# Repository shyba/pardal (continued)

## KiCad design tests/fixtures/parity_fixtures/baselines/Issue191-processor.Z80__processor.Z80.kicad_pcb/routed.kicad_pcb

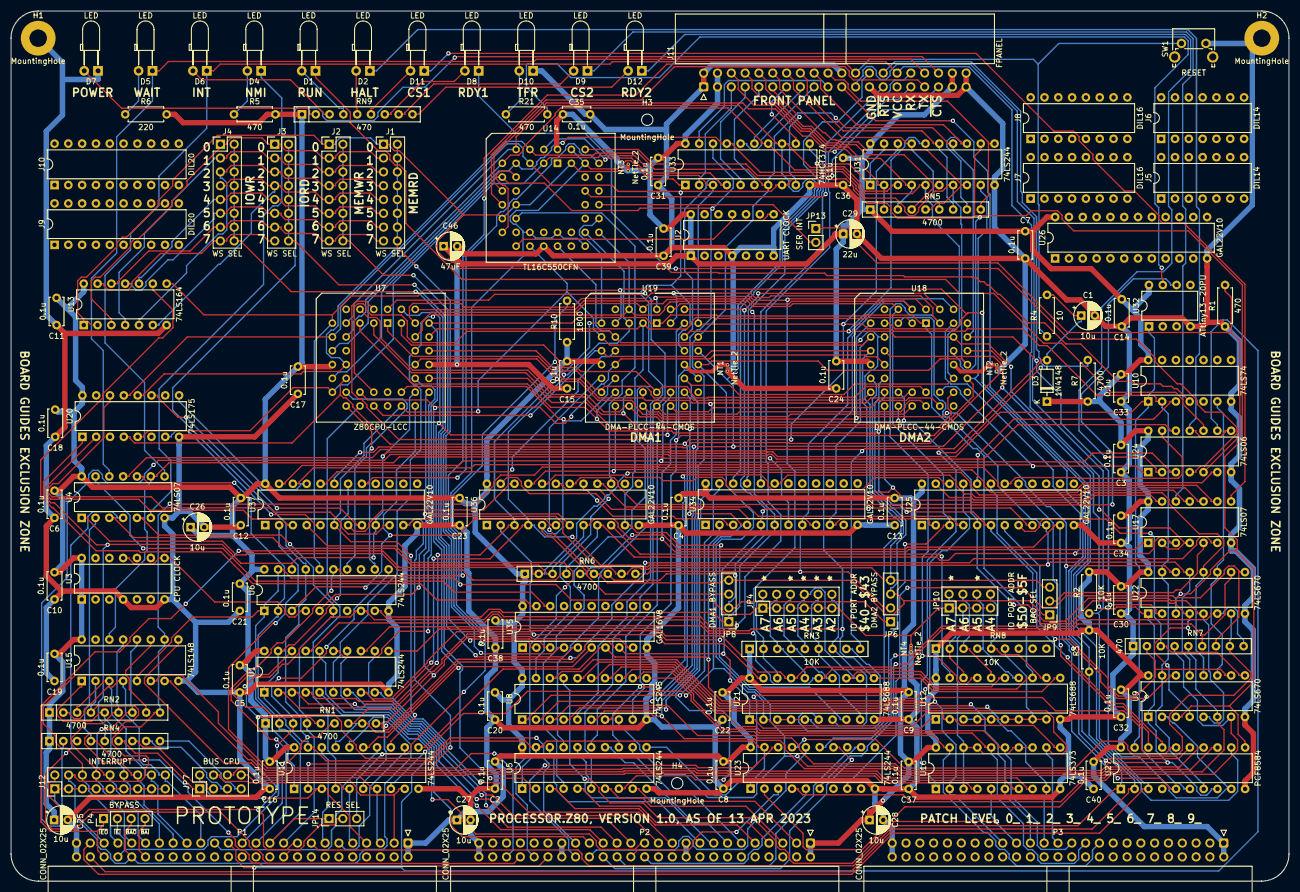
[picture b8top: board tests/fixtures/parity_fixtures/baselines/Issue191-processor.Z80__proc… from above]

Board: 2 copper layers, 235.0 x 160.0 mm, 138 parts (0 on the bottom side), 244 nets.

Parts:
C1, C25, C26, C27, C28: 10u; CP_Radial_D5.0mm_P2.50mm
C2, C3, C4, C5, C6, C7, C8, C9, C10, C11, C12, C13, C14, C15, C16, C17, C18, C19, C20, C21, C22, C23, C24, C30, C31, C32, C33, C34, C35, C36, C37, C38, C39, C40: 0.1u; C_Disc_D5.0mm_W2.5mm_P5.00mm
C29: 22u; CP_Radial_D5.0mm_P2.50mm
C46: 47uF; CP_Radial_D5.0mm_P2.50mm
D1, D2, D4, D5, D6, D7, D8, D9, D10, D11, D12: LED; LED_D3.0mm_Horizontal_O3.81mm_Z2.0mm
D3: 1N4148; D_DO-35_SOD27_P7.62mm_Horizontal
H1, H2: MountingHole; MountingHole_3.2mm_M3_Pad
H3, H4: MountingHole; MountingHole_2.1mm
J1, J2, J3, J4: WS SEL; PinHeader_2x08_P2.54mm_Vertical
J5, J6: DIL14; DIP-14_W7.62mm
J7, J8: DIL16; DIP-16_W7.62mm
J9, J10: DIL20; DIP-20_W7.62mm
J11: FPANEL; IDC-Header_2x20_P2.54mm_Horizontal
J12: INTERRUPT; PinHeader_2x09_P2.54mm_Vertical
JP4: IO PORT ADDR; PinHeader_2x06_P2.54mm_Vertical
JP6: DMA2 BYPASS; PinHeader_1x04_P2.54mm_Vertical
JP7: BUS CPU; PinHeader_2x04_P2.54mm_Vertical
JP8: DMA1 BYPASS; PinHeader_1x04_P2.54mm_Vertical
JP9: BAO SEL; PinHeader_1x03_P2.54mm_Vertical
JP10: IO PORT ADDR; PinHeader_2x04_P2.54mm_Vertical
JP13: SER INT; PinHeader_1x02_P2.54mm_Vertical
JP14: RES SEL; PinHeader_1x03_P2.54mm_Vertical
NT1, NT2, NT3, NT4: NetTie_2; NetTie-2_THT_Pad0.3mm
P1, P2, P3: CONN_02X25; IDC-Header_2x25_P2.54mm_Horizontal
P4: BYPASS; PinHeader_1x04_P2.54mm_Vertical
R1, R5, R21: 470; R_Axial_DIN0207_L6.3mm_D2.5mm_P7.62mm_Horizontal
R2, R3: 10K; R_Axial_DIN0207_L6.3mm_D2.5mm_P7.62mm_Horizontal
R4: 10; R_Axial_DIN0207_L6.3mm_D2.5mm_P7.62mm_Horizontal
R6: 220; R_Axial_DIN0207_L6.3mm_D2.5mm_P7.62mm_Horizontal
R7: 4700; R_Axial_DIN0207_L6.3mm_D2.5mm_P7.62mm_Horizontal
R10: 1800; R_Axial_DIN0207_L6.3mm_D2.5mm_P7.62mm_Horizontal
RN1, RN2, RN4, RN5, RN6: 4700; R_Array_SIP9
RN3, RN8: 10K; R_Array_SIP9
RN7, RN9: 470; R_Array_SIP9
SW1: RESET; SW_Tactile_SPST_Angled_PTS645Vx58-2LFS
U1, U5, U6, U11, U23, U31: 74LS244; DIP-20_W7.62mm
U2: UART CLOCK; DIP-14_W7.62mm
U3: CPU CLOCK; DIP-14_W7.62mm
U4, U17: 74LS07; DIP-14_W7.62mm
U7: Z80CPU-LCC; PLCC-44_THT-Socket
U8: 74LS245; DIP-20_W7.62mm
U9, U22: 74LS670; DIP-16_W7.62mm
U10: 74LS74; DIP-14_W7.62mm
U12, U21: 74LS688; DIP-20_W7.62mm
U13: 74LS164; DIP-14_W7.62mm
U14: TL16C550CFN; PLCC-44_THT-Socket
U15: 74LS148; DIP-16_W7.62mm
U16: 74LS373; DIP-20_W7.62mm
U18, U19: DMA-PLCC-44-CMOS; PLCC-44_THT-Socket
U20: 74LS175; DIP-16_W7.62mm
U24: 74LS06; DIP-14_W7.62mm
U25, U26, U34, U36, U37: GAL22V10; DIP-24_W7.62mm
U27: PCF8584; DIP-20_W7.62mm
U32: ATtiny13-20PU; DIP-8_W7.62mm
U33: 74HCT374; DIP-20_W7.62mm
U35: GAL16V8; DIP-20_W7.62mm

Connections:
10KA: C1.1, D3.2 (A), R4.2, RN3.9 (R8), U4.11
470A: D7.2 (A), RN9.2 (R1)
470B: D6.2 (A), RN9.3 (R2)
470C: D1.2 (A), RN9.4 (R3)
470D: D2.2 (A), RN9.5 (R4)
470E: D11.2 (A), RN9.6 (R5)
470F: D8.2 (A), RN9.7 (R6)
470G: D9.2 (A), RN9.8 (R7)
470H: D12.2 (A), RN9.9 (R8)
+12V: P2.19, P2.20
-12V: P2.37, P2.38
/DMA/GND-DMA1: NT1.2, U19.34 (GND)
/DMA/GND-DMA2: NT2.2, U18.34 (GND)
/fpanel/FP-D0: J11.6, RN5.2 (R1), U31.2 (1A0)
/fpanel/FP-D1: J11.8, RN5.3 (R2), U31.4 (1A1)
/fpanel/FP-D2: J11.10, RN5.4 (R3), U31.6 (1A2)
/fpanel/FP-D3: J11.12, RN5.5 (R4), U31.8 (1A3)
/fpanel/FP-D4: J11.14, RN5.6 (R5), U31.17 (2A0)
/fpanel/FP-D5: J11.16, RN5.7 (R6), U31.15 (2A1)
/fpanel/FP-D6: J11.18, RN5.8 (R7), U31.13 (2A2)
/fpanel/FP-D7: J11.20, RN5.9 (R8), U31.11 (2A3)
/waitstate/1WS: J1.3, J2.3, J3.1, J4.1, U13.3 (Q0)
/waitstate/2WS: J1.5, J2.5, J3.3, J4.3, U13.4 (Q1)
/waitstate/3WS: J1.7, J2.7, J3.5, J4.5, U13.5 (Q2)
/waitstate/4WS: J1.9, J2.9, J3.7, J4.7, U13.6 (Q3)
/waitstate/5WS: J1.11, J2.11, J3.9, J4.9, U13.10 (Q4)
/waitstate/6WS: J1.13, J2.13, J3.11, J4.11, U13.11 (Q5)
/waitstate/7WS: J1.15, J2.15, J3.13, J4.13, U13.12 (Q6)
/waitstate/8WS: J3.15, J4.15, U13.13 (Q7)
A0: P2.35, U1.18 (1Y0)
A1: P2.33, U1.16 (1Y1)
A2: P2.31, U1.14 (1Y2)
A3: P2.29, U1.12 (1Y3)
A4: P2.27, U1.3 (2Y0)
A5: P2.25, U1.5 (2Y1)
A6: P2.23, U1.7 (2Y2)
A7: P2.21, U1.9 (2Y3)
A8: P2.17, U5.18 (1Y0)
A9: P2.15, U5.16 (1Y1)
A10: P2.13, U5.14 (1Y2)
A11: P2.11, U5.12 (1Y3)
A12: P2.9, U5.3 (2Y0)
A13: P2.7, U5.5 (2Y1)
A14: P2.5, U5.7 (2Y2)
A15: P2.3, U5.9 (2Y3)
A16: P2.36, U23.18 (1Y0)
A17: P2.34, U23.16 (1Y1)
A18: P2.32, U23.14 (1Y2)
A19: P2.30, U23.12 (1Y3)
A20: P2.28, U23.3 (2Y0)
A21: P2.26, U23.5 (2Y1)
BUSACK: U1.1 (1OE), U1.19 (2OE), U5.1 (1OE), U5.19 (2OE), U11.19 (2OE), U23.1 (1OE), U23.19 (2OE), U37.18 (O5)
CLK: P1.15, U6.16 (1Y1), U7.7 (CLK), U13.8 (CP), U18.8 (CLK), U19.8 (CLK), U27.1 (CLK)
CPU-A0: U1.2 (1A0), U7.34 (A0), U9.14 (Wa), U14.31 (A0), U18.7 (A0), U19.7 (A0), U22.14 (Wa), U27.6 (A0), U36.3 (I2)
CPU-A1: U1.4 (1A1), U7.35 (A1), U9.13 (Wb), U14.30 (A1), U18.5 (A1), U19.5 (A1), U22.13 (Wb), U25.10 (I9), U36.4 (I3)
CPU-A2: U1.6 (1A2), U7.36 (A2), U14.29 (A2), U18.4 (A2), U19.4 (A2), U21.6 (P2), U25.3 (I2)
CPU-A3: U1.8 (1A3), U7.37 (A3), U18.3 (A3), U19.3 (A3), U21.8 (P3), U36.11 (I10)
CPU-A4: U1.17 (2A0), U7.38 (A4), U12.11 (P4), U18.2 (A4), U19.2 (A4), U21.11 (P4)
CPU-A5: U1.15 (2A1), U7.39 (A5), U12.13 (P5), U18.1 (A5), U19.1 (A5), U21.13 (P5)
CPU-A6: U1.13 (2A2), U7.40 (A6), U12.15 (P6), U18.44 (A6), U19.44 (A6), U21.15 (P6)
CPU-A7: U1.11 (2A3), U7.41 (A7), U12.17 (P7), U18.43 (A7), U19.43 (A7), U21.17 (P7)
CPU-A8: U5.2 (1A0), U7.42 (A8), U18.26 (A8), U19.26 (A8)
CPU-A9: U5.4 (1A1), U7.43 (A9), U18.25 (A9), U19.25 (A9)
CPU-A10: U5.6 (1A2), U7.44 (A10), U18.24 (A10), U19.24 (A10)
CPU-A11: U5.8 (1A3), U7.1 (A11), U18.23 (A11), U19.23 (A11)
CPU-A12: U5.17 (2A0), U7.2 (A12), U18.22 (A12), U19.22 (A12)
CPU-A13: U5.15 (2A1), U7.3 (A13), U18.21 (A13), U19.21 (A13)
CPU-A14: U7.4 (A14), U9.5 (Ra), U18.20 (A14), U19.20 (A14), U22.5 (Ra), U25.5 (I4)
CPU-A15: U7.5 (A15), U9.4 (Rb), U18.19 (A15), U19.19 (A15), U22.4 (Rb), U25.6 (I5)
CPU-D0: U7.16 (D0), U8.2 (A0), U9.15 (D1), U10.2 (D), U14.2 (D0), U18.39 (D0), U19.39 (D0), U20.4 (D0), U22.15 (D1), U27.7 (D0), U31.18 (1Y0), U33.3 (D0)
CPU-D1: U7.17 (D1), U8.3 (A1), U9.1 (D2), U14.3 (D1), U18.38 (D1), U19.38 (D1), U20.5 (D1), U22.1 (D2), U27.8 (D1), U31.16 (1Y1), U33.4 (D1)
CPU-D2: U7.14 (D2), U8.4 (A2), U9.2 (D3), U14.4 (D2), U18.37 (D2), U19.37 (D2), U20.12 (D2), U22.2 (D3), U27.9 (D2), U31.14 (1Y2), U33.7 (D2)
CPU-D3: U7.9 (D3), U8.5 (A3), U9.3 (D4), U14.5 (D3), U18.36 (D3), U19.36 (D3), U20.13 (D3), U22.3 (D4), U27.11 (D3), U31.12 (1Y3), U33.8 (D3)
CPU-D4: U7.8 (D4), U8.6 (A4), U14.6 (D4), U18.35 (D4), U19.35 (D4), U27.12 (D4), U31.3 (2Y0), U33.13 (D4)
CPU-D5: U7.10 (D5), U8.7 (A5), U14.7 (D5), U18.32 (D5), U19.32 (D5), U27.13 (D5), U31.5 (2Y1), U33.14 (D5)
CPU-D6: U7.11 (D6), U8.8 (A6), U14.8 (D6), U18.33 (D6), U19.33 (D6), U27.14 (D6), U31.7 (2Y2), U33.17 (D6)
CPU-D7: U7.15 (D7), U8.9 (A7), U14.9 (D7), U18.31 (D7), U19.31 (D7), U27.15 (D7), U31.9 (2Y3), U33.18 (D7)
D0: P3.33, U8.18 (B0), U16.2 (O0)
D1: P3.31, U8.17 (B1), U16.5 (O1)
D2: P3.29, U8.16 (B2), U16.6 (O2)
D3: P3.27, U8.15 (B3), U16.9 (O3)
D4: P3.25, U8.14 (B4), U16.12 (O4)
D5: P3.23, U8.13 (B5), U16.15 (O5)
D6: P3.21, U8.12 (B6), U16.16 (O6)
D7: P3.19, U8.11 (B7), U16.19 (O7)
DATA-DIR: U8.1 (A->B), U34.23 (O0)
DATA_XFER: U32.6 (PB1), U36.18 (O5)
DMA-RDY1: U19.27 (RDY), U24.3, U37.23 (O0)
DMA-RDY2: U18.27 (RDY), U24.1, U37.22 (O1)
FP-LATCH-WR: U33.11 (Cp), U34.20 (O3)
GND: C1.2, C2.2, C3.2, C4.2, C5.2, C6.2, C7.2, C8.2, C9.2, C10.2, C11.2, C12.2, C13.2, C14.2, C15.2, C16.2, C17.2, C18.2, C19.2, C20.2, C21.2, C22.2, C23.2, C24.2, C25.2, C26.2, C27.2, C28.2, C29.2, C30.2, C31.2, C32.2, C33.2, C34.2, C35.2, C36.2, C37.2, C38.2, C39.2, C40.2, C46.2, D7.1 (K), D10.1 (K), H1.1, H2.1, J11.1, J11.2, J11.22, J11.25, J11.39, J11.40, NT1.1, NT2.1, NT4.1, P1.49, P1.50, P2.49, P2.50, P3.49, P3.50, R1.1, RN7.1 (common), SW1.2, U1.10 (GND), U2.4, U2.7, U3.4, U3.7, U4.7 (GND), U5.10 (GND), U6.10 (GND), U7.33 (GND), U8.10 (GND), U9.8 (GND), U10.7 (GND), U11.10 (GND), U12.10 (GND), U13.7 (GND), U14.22 (GND), U15.8 (GND), U16.10 (GND), U17.7 (GND), U20.8 (GND), U21.10 (GND), U22.8 (GND), U23.10 (GND), U24.7 (GND), U25.12 (GND), U26.12 (GND), U27.10 (VSS), U31.10 (GND), U32.4 (GND), U33.10 (GND), U34.12 (GND), U35.10 (GND), U36.12 (GND), U37.12 (GND)
I2C_SCL: J11.23, P1.47, R2.1, U27.3 (SCL)
I2C_SDA: J11.21, P1.48, R3.1, U27.2 (SDA)
INT: JP13.1 (A), R1.2, U24.5
INT-I2C: U24.13, U25.18 (O5)
IO-SEL: U34.3 (I2), U36.17 (O6)
unnamed: D1.1 (K), U24.10
unnamed: D2.1 (K), U24.8, U24.11
unnamed: D4.1 (K), U4.6
unnamed: D4.2 (A), R5.1
unnamed: D5.2 (A), R6.1
unnamed: D8.1 (K), U24.4
unnamed: D9.1 (K), U17.12
unnamed: D10.2 (A), R21.1
unnamed: D11.1 (K), U17.8
unnamed: D12.1 (K), U24.2
unnamed: J11.5, U33.2 (O0)
unnamed: J11.7, U33.5 (O1)
unnamed: J11.9, U33.6 (O2)
unnamed: J11.11, U33.9 (O3)
unnamed: J11.13, U33.12 (O4)
unnamed: J11.15, U33.15 (O5)
unnamed: J11.17, U33.16 (O6)
unnamed: J11.19, U33.19 (O7)
unnamed: J12.1, J12.3, J12.5, J12.7, J12.9, J12.11, J12.13, J12.15, J12.17, U24.12
unnamed: JP4.2, RN3.2 (R1), U21.18 (R7)
unnamed: JP4.4, RN3.3 (R2), U21.16 (R6)
unnamed: JP4.6, RN3.4 (R3), U21.14 (R5)
unnamed: JP4.8, RN3.5 (R4), U21.12 (R4)
unnamed: JP4.10, RN3.6 (R5), U21.9 (R3)
unnamed: JP4.12, RN3.7 (R6), U21.7 (R2)
unnamed: JP7.1, RN4.6 (R5)
unnamed: JP7.3, RN4.7 (R6)
unnamed: JP7.5, RN4.8 (R7)
unnamed: JP7.7, RN4.9 (R8)
unnamed: JP9.2, U17.5
unnamed: JP10.2, RN8.2 (R1), U12.18 (R7)
unnamed: JP10.4, RN8.3 (R2), U12.16 (R6)
unnamed: JP10.6, RN8.4 (R3), U12.14 (R5)
unnamed: JP10.8, RN8.5 (R4), U12.12 (R4)
unnamed: JP13.2 (B), U14.33 (INTR)
unnamed: R21.2, U32.7 (PB2)
unnamed: RN3.8 (R7), U21.3 (R0), U21.4 (P1), U21.5 (R1)
unnamed: RN8.6 (R5), U12.3 (R0), U12.4 (P1), U12.5 (R1), U12.6 (P2), U12.7 (R2), U12.8 (P3), U12.9 (R3)
unnamed: U14.10 (RCLK), U14.17 (~BAUDOUT)
unnamed: U15.6 (S2), U16.8 (D3)
unnamed: U15.7 (S1), U16.7 (D2)
unnamed: U15.9 (S0), U16.4 (D1)
ONE: J1.1, J2.1, NT3.2, U10.4 (~S), U13.1 (DSA), U13.2 (DSB), U14.14 (CS0), U14.15 (CS1), U14.43 (~RI)
RAW-CLK: U3.8, U3.11, U6.4 (1A1)
RDY_Q0: U20.2 (Q0), U37.3 (I2)
RDY_Q1: U20.7 (Q1), U37.5 (I4)
READY: U4.13, U35.18 (IO2)
RESET: U14.39 (MR), U37.17 (O6)
RX: J11.31, U14.11 (SIN)
SEL-A14: U5.13 (2A2), U25.22 (O1)
SEL-A15: U5.11 (2A3), U25.21 (O2)
TX: J11.33, U14.13 (SOUT)
UART-CLK: U2.8, U2.11, U14.18 (XIN)
VCC: C2.1, C3.1, C4.1, C5.1, C6.1, C7.1, C8.1, C9.1, C10.1, C11.1, C12.1, C13.1, C14.1, C15.1, C16.1, C17.1, C18.1, C19.1, C20.1, C21.1, C22.1, C23.1, C24.1, C25.1, C26.1, C27.1, C28.1, C29.1, C30.1, C31.1, C32.1, C33.1, C34.1, C35.1, C36.1, C37.1, C38.1, C39.1, C40.1, C46.1, D3.1 (K), J11.3, J11.4, J11.37, J11.38, NT3.1, P1.1, P1.2, P2.1, P2.2, P3.1, P3.2, R2.2, R3.2, R5.2, R6.2, R7.1, R10.1, RN1.1 (common), RN2.1 (common), RN3.1 (common), RN4.1 (common), RN5.1 (common), RN6.1 (common), RN8.1 (common), RN9.1 (common), U1.20 (VCC), U2.1, U2.14, U3.1, U3.14, U4.14 (VCC), U5.20 (VCC), U6.20 (VCC), U7.13 (+5V), U8.20 (VCC), U9.16 (VCC), U10.14 (VCC), U11.20 (VCC), U12.20 (VCC), U13.14 (VCC), U14.44 (VCC), U15.16 (VCC), U16.20 (VCC), U17.14 (VCC), U18.13 (VCC), U19.13 (VCC), U20.16 (VCC), U21.20 (VCC), U22.16 (VCC), U23.20 (VCC), U24.14 (VCC), U25.24 (VCC), U26.24 (VCC), U27.20 (VDD), U31.20 (VCC), U32.8 (VCC), U33.20 (VCC), U34.24 (VCC), U35.20 (VCC), U36.24 (VCC), U37.24 (VCC)
WS-IORD: J3.2, J3.4, J3.6, J3.8, J3.10, J3.12, J3.14, J3.16, U35.3 (I3)
WS-IOWR: J4.2, J4.4, J4.6, J4.8, J4.10, J4.12, J4.14, J4.16, U35.5 (I5)
WS-MEMRD: J1.2, J1.4, J1.6, J1.8, J1.10, J1.12, J1.14, J1.16, U35.2 (I2)
WS-MEMWR: J2.2, J2.4, J2.6, J2.8, J2.10, J2.12, J2.14, J2.16, U35.4 (I4)
ZERO: JP4.1, JP4.3, JP4.5, JP4.7, JP4.9, JP4.11, JP10.1, JP10.3, JP10.5, JP10.7, NT4.2, U6.1 (1OE), U6.19 (2OE), U11.1 (1OE), U14.21 (WR), U14.25 (RD), U14.28 (~ADS), U14.41 (~DSR), U14.42 (~DCD), U15.5 (EI), U16.3 (D0), U16.13 (D4), U16.14 (D5), U16.17 (D6), U16.18 (D7), U33.1 (OE)
mA14: RN7.2 (R1), U9.10 (Q1), U25.7 (I6)
mA15: RN7.3 (R2), U9.9 (Q2), U25.8 (I7)
mA16: RN7.4 (R3), U9.7 (Q3), U23.2 (1A0)
mA17: RN7.5 (R4), U9.6 (Q4), U23.4 (1A1)
mA18: RN7.6 (R5), U22.10 (Q1), U23.6 (1A2)
mA19: RN7.7 (R6), U22.9 (Q2), U23.8 (1A3)
mA20: RN7.8 (R7), U22.7 (Q3), U23.17 (2A0)
mA21: RN7.9 (R8), U22.6 (Q4), U23.15 (2A1)
~BAI: P1.40, P4.4
~BAO: P1.42, P4.3, RN1.9 (R8), RN4.2 (R1), U17.6
~BUS-EN: U8.19 (CE), U36.19 (O4)
~BUSACK: P1.13, U11.18 (1Y0)
~BUSRQ: P1.23, R10.2, U6.15 (2A1), U18.17 (~BUSREQ), U19.17 (~BUSREQ)
~CE_DMA_RDY: U36.22 (O1), U37.7 (I6)
~CPU-BUSACK: JP8.3, U7.27 (BUSACK), U19.16 (~BAI), U36.5 (I4)
~CPU-BUSRQ: U6.5 (2Y1), U7.29 (BUSRQ), U36.7 (I6)
~CPU-HALT: U7.20 (HALT), U11.4 (1A1)
~CPU-INT: U6.12 (1Y3), U7.18 (INT)
~CPU-IORQ: RN1.8 (R7), U7.22 (IOREQ), U11.17 (2A0), U12.1 (G), U18.11 (~IORQ), U19.11 (~IORQ), U21.1 (G), U25.9 (I8), U34.5 (I4), U35.8 (I8)
~CPU-M1: U7.31 (M1), U11.8 (1A3), U12.2 (P0), U16.11 (LE), U18.30 (~M1), U19.30 (~M1), U21.2 (P0), U34.4 (I3)
~CPU-MREQ: U7.21 (MREQ), U11.15 (2A1), U18.14 (~MREQ), U19.14 (~MREQ), U35.6 (I6)
~CPU-NMI: U6.14 (1Y2), U7.19 (NMI)
~CPU-RD: U7.23 (RD), U11.11 (2A3), U14.24 (~RD), U18.10 (~RD), U19.10 (~RD), U27.16 (~RD), U34.2 (I1), U35.7 (I7)
~CPU-RESET: RN4.5 (R4), U6.18 (1Y0), U7.30 (RESET), U10.1 (~R), U20.1 (~Mr), U27.19 (~RST), U32.1 (~RESET/PB5), U37.9 (I8)
~CPU-RFSH: U7.32 (RFSH), U11.6 (1A2), U35.9 (I9)
~CPU-WAIT: U6.3 (2Y0), U7.28 (WAIT), U36.6 (I5)
~CPU-WR: U7.26 (WR), U11.13 (2A2), U14.20 (~WR), U18.9 (~WR), U19.9 (~WR), U25.2 (I1), U34.10 (I9), U37.6 (I5)
~CS_I2C_WR: U25.17 (O6), U27.18 (~WR)
~CS_I2C: U25.19 (O4), U27.17 (~CS)
~CS_IO: U12.19 (P=R), U36.10 (I9)
~CS_MAP: U25.4 (I3), U36.16 (O7)
~CS_UART: U14.16 (~CS2), U36.15 (O8)
~CTS: J11.35, U14.40 (~CTS)
~DMA-ADDR: RN1.7 (R6), U21.19 (P=R), U36.2 (I1)
~DMA-BAO1: JP6.3, JP8.4, JP9.1, RN6.6 (R5), U18.16 (~BAI), U19.15 (~BA0)
~DMA-BAO2: JP6.4, JP9.3, RN6.8 (R7), U11.2 (1A0), U18.15 (~BA0), U37.11 (I10)
~DMA-CS1: U17.9, U19.18 (~CE/WAIT), U36.21 (O2)
~DMA-CS2: U17.13, U18.18 (~CE/WAIT), U36.20 (O3)
~DMA-IEI1: JP8.1, U6.9 (2Y3), U19.42 (IEI), U34.6 (I5)
~DMA-IEO1: JP6.1, JP8.2, RN6.7 (R6), U18.42 (IEI), U19.40 (IEO)
~DMA-IEO2: JP6.2, RN6.9 (R8), U18.40 (IEO), U34.8 (I7)
~DMA-INT-PULSE1: RN6.3 (R2), U4.3, U17.1, U19.41 (~INT/PULSE), U36.8 (I7)
~DMA-INT-PULSE2: RN6.4 (R3), U4.1, U17.3, U18.41 (~INT/PULSE), U36.9 (I8)
~DMA-RESET1: U19.12 (~RESET), U37.20 (O3)
~DMA-RESET2: U18.12 (~RESET), U37.19 (O4)
~DMA_RDY_WR: U20.9 (Cp), U37.21 (O2)
~DREQ0: P2.46, U37.2 (I1)
~DREQ1: P2.42, U37.4 (I3)
~EIRQ0: J12.4, P1.45, RN2.9 (R8), U15.10 (IO), U24.6
~EIRQ1: J12.6, P1.43, RN2.8 (R7), U15.11 (I1)
~EIRQ2: J12.8, P1.41, RN2.7 (R6), U15.12 (I2)
~EIRQ3: J12.10, P1.39, RN2.6 (R5), U15.13 (I3)
~EIRQ4: J12.12, P1.37, RN2.5 (R4), U15.1 (I4)
~EIRQ5: J12.14, P1.35, RN2.4 (R3), U15.2 (I5)
~EIRQ6: J12.16, P1.33, RN2.3 (R2), U15.3 (I6)
~EIRQ7: J12.18, P1.31, RN2.2 (R1), U15.4 (I7)
~EXT_RES: J11.24, JP14.3, R4.1, SW1.1
~FP-LATCH-RD: U31.1 (1OE), U31.19 (2OE), U34.21 (O2)
~FP-LATCH: U34.9 (I8), U36.23 (O0)
~HALT: P1.27, U11.16 (1Y1), U24.9
~IEI: P1.44, P4.2, RN1.3 (R2), U6.11 (2A3)
~IEO: P1.46, P4.1, RN6.2 (R1), U17.10
~IM2-EN-OE: J11.28, R7.2, U16.1 (OE)
~IM2-EN: J11.26, U34.22 (O1)
~IM2-IEO: U17.11, U34.19 (O4)
~IM2-INT: U4.9, U15.14 (GS), U34.7 (I6)
~INT0-EN: D6.1 (K), J11.30, U4.8, U17.2, U17.4
~INT0: J11.32, J12.2, P1.17, RN1.5 (R4), U6.8 (1A3)
~INT-I2C: RN6.5 (R4), U25.11 (I10), U27.5 (~INT)
~IORQ: JP7.2, P1.7, U11.3 (2Y0)
~M1: P1.11, U11.12 (1Y3)
~MREQ: JP7.4, P1.9, U11.5 (2Y1)
~MR: U13.9 (~MR), U35.19 (IO1)
~NMI: P1.19, RN1.4 (R3), U4.5, U6.6 (1A2)
~PAGE_EN: U9.11 (~Er), U10.6 (~Q), U22.11 (~Er)
~PAGE_WR: U9.12 (~Ew), U22.12 (~Ew), U25.23 (O0)
~PGEN_WR: U10.3 (C), U25.20 (O3)
~RD: JP7.8, P1.3, U11.9 (2Y3)
~RES_IN: JP14.2, P1.20
~RES_OUT: JP14.1, P1.21, RN1.2 (R1), U4.10, U6.2 (1A0)
~RFSH: P1.29, U11.14 (1Y2)
~RTS: J11.27, U14.36 (~RTS)
~TEND0: P2.44, RN4.3 (R2), U4.4
~TEND1: P2.40, RN4.4 (R3), U4.2
~USR-RESET1: U20.11 (~Q2), U37.8 (I7)
~USR-RESET2: U20.14 (~Q3), U37.10 (I9)
~WAIT-EN: D5.1 (K), J11.34, U4.12
~WAIT: J11.36, P1.25, RN1.6 (R5), U6.17 (2A0)
~WR: JP7.6, P1.5, U11.7 (2Y2)

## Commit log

2025-12-24 Initial
2025-12-24 example pic
2025-12-24 remove bad paths, update tests, skip incomplete features tests
2025-12-24 more tests, better docs
2025-12-25 better DRC, 4 layer support, examples, more tests
2025-12-26 faster
2026-01-17 routing
2026-01-23 Parity tooling, benchmarks, and doc consolidation
2026-01-23 Baseline tooling: summaries, Mojo-vs-baseline checks, backend-route CLI
2026-01-24 Add Mojo-vs-baseline suite runner and report
2026-01-24 Decompose remaining parity work into chunked plan
2026-01-24 Add per-step timeouts to docker routing pipeline
2026-03-07 Freerouting in mojo
2026-06-05 working full dsl
